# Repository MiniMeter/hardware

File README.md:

# hardware
MiniMeter PCB (designed in KiCad)

<div align="center">
    
</div>
<div align="center">
    
</div>
<div align="center">
    
</div>

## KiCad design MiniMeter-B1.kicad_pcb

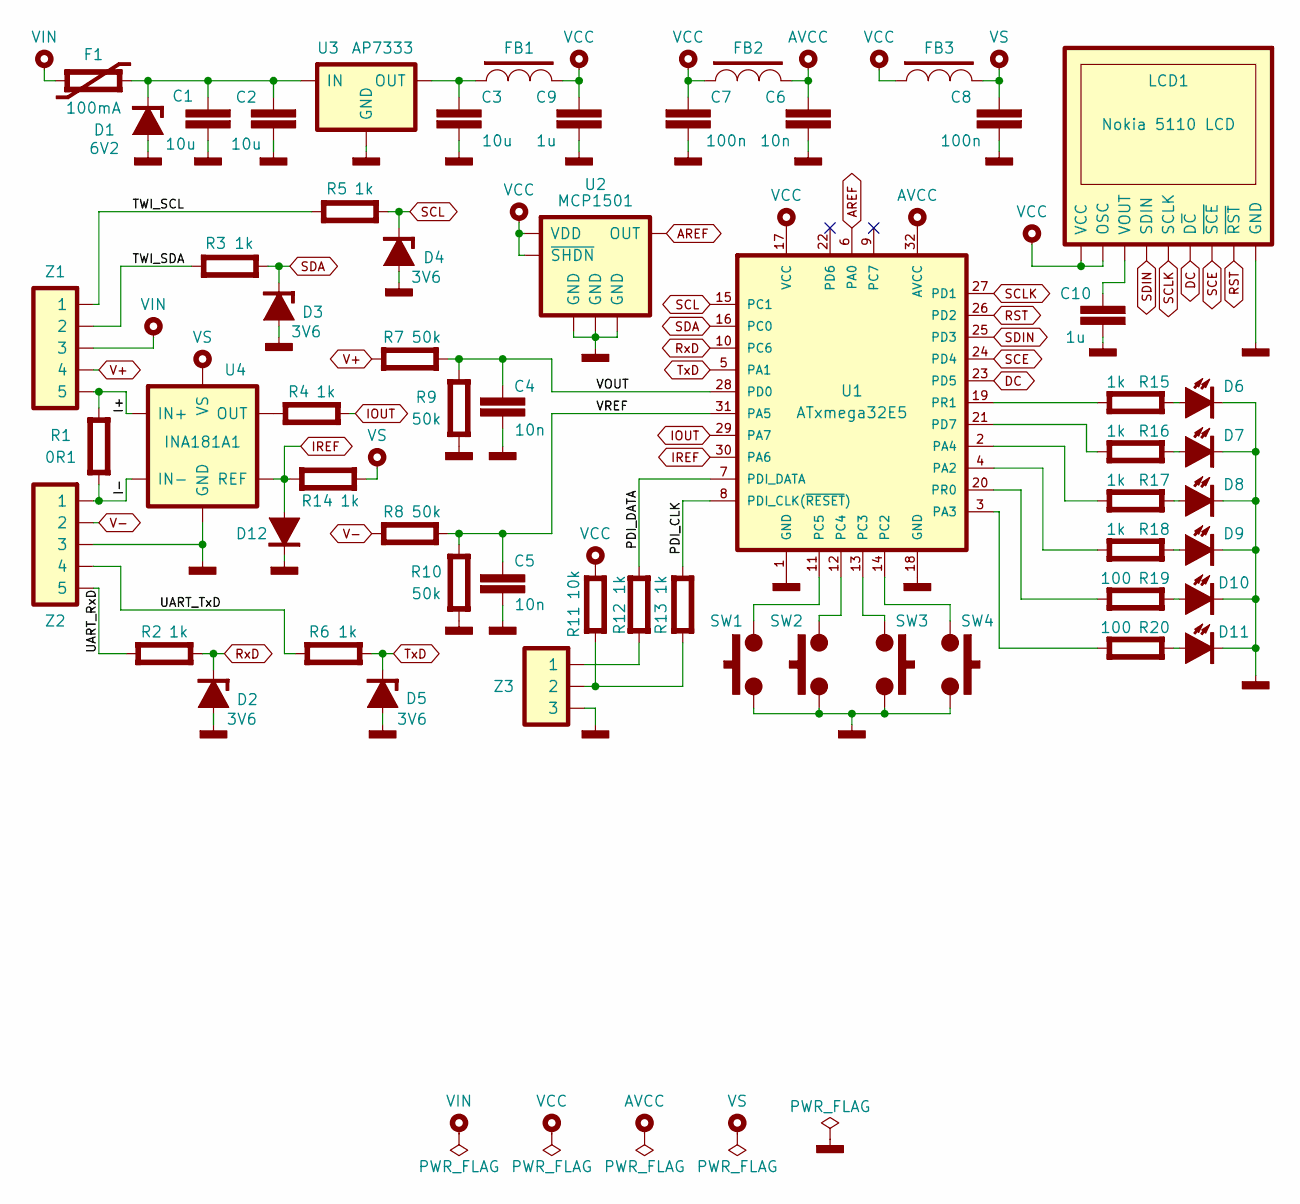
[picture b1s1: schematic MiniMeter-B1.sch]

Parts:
C1, C2, C3: 10u; SMD_2012_(0805)
C4, C5, C6: 10n; SMD_2012_(0805)
C7, C8: 100n; SMD_2012_(0805)
C9, C10: 1u; SMD_2012_(0805)
D1: 6V2; SMD_SOD-123
D2, D3, D4, D5: 3V6; SMD_SOD-323
D6, D7, D8, D9: LED-G; SMD_2012_(0805)+
D10, D11: LED-B; SMD_2012_(0805)+
D12: 1N4148; SMD_SOD-323
F1: 100mA; SMD_2012_(0805)
FB1, FB2, FB3: ferrite bead; SMD_2012_(0805)
LCD1: Nokia 5110 LCD; LCD_Nokia-5110
R1: 0R1; SMD_3216_(1206)
R2, R3, R4, R5, R6, R12, R13, R14, R15, R16, R17, R18: 1k; SMD_2012_(0805)
R7, R8, R9, R10: 50k; SMD_2012_(0805)
R11: 10k; SMD_2012_(0805)
R19, R20: 100; SMD_2012_(0805)
SW1, SW2, SW3, SW4: uSwitch 3x6mm; THT_uSwitch_3x6mm
U1: ATxmega32E5; SMD_TQFP-32_7x7mm
U2: MCP1501; SMD_SOT-23-6
U3: AP7333; SMD_SOT-23-3
U4: INA181A1; SMD_SOT-23-6
Z1, Z2: goldpin 1x5; THT_Goldpin-1x5
Z3: goldpin 1x3; THT_Goldpin-1x3

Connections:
/I+: R1.1, U4.3 (IN+), Z1.5
/I-: R1.2, U4.4 (IN-), Z2.1
/PDI_CLK: R13.2, U1.8 (PDI_CLK(~RESET~))
/PDI_DATA: R12.1, U1.7 (PDI_DATA)
/TWI_SCL: R5.2, Z1.1
/TWI_SDA: R3.2, Z1.2
/UART_RxD: R2.2, Z2.5
/UART_TxD: R6.2, Z2.4
/VOUT: C4.1, R7.1, R9.2, U1.28 (PD0)
/VREF: C5.1, R8.1, R10.2, U1.31 (PA5)
AREF: U1.6 (PA0), U2.1 (OUT)
AVCC: C6.1, FB2.2, U1.32 (AVCC)
DC: LCD1.6 (D~C), U1.23 (PD5)
GND: C1.2, C2.2, C3.2, C4.2, C5.2, C6.2, C7.2, C8.2, C9.2, C10.1, D1.2 (A), D2.2 (A), D3.2 (A), D4.2 (A), D5.2 (A), D6.1 (K), D7.1 (K), D8.1 (K), D9.1 (K), D10.1 (K), D11.1 (K), D12.1 (K), LCD1.3 (GND), R9.1, R10.1, SW1.2, SW2.2, SW3.2, SW4.2, U1.1 (GND), U1.18 (GND), U2.2 (GND), U2.3 (GND), U2.5 (GND), U3.3 (GND), U4.2 (GND), Z2.3, Z3.3
IOUT: R4.1, U1.29 (PA7)
IREF: D12.2 (A), R14.2, U1.30 (PA6), U4.5 (REF)
unnamed: C1.1, C2.1, D1.1 (K), F1.2, U3.1 (IN)
unnamed: C3.1, FB1.1, U3.2 (OUT)
unnamed: C10.2, LCD1.2 (VOUT)
unnamed: D6.2 (A), R15.2
unnamed: D7.2 (A), R16.2
unnamed: D8.2 (A), R17.2
unnamed: D9.2 (A), R18.2
unnamed: D10.2 (A), R19.2
unnamed: D11.2 (A), R20.2
unnamed: R4.2, U4.1 (OUT)
unnamed: R11.1, R13.1, Z3.2
unnamed: R12.2, Z3.1
unnamed: R15.1, U1.19 (PR1)
unnamed: R16.1, U1.21 (PD7)
unnamed: R17.1, U1.2 (PA4)
unnamed: R18.1, U1.4 (PA2)
unnamed: R19.1, U1.20 (PR0)
unnamed: R20.1, U1.3 (PA3)
unnamed: SW1.1, U1.11 (PC5)
unnamed: SW2.1, U1.12 (PC4)
unnamed: SW3.1, U1.13 (PC3)
unnamed: SW4.1, U1.14 (PC2)
RST: LCD1.1 (~RST), U1.26 (PD2)
RxD: D2.1 (K), R2.1, U1.10 (PC6)
SCE: LCD1.5 (~SCE), U1.24 (PD4)
SCL: D4.1 (K), R5.1, U1.15 (PC1)
SCLK: LCD1.8 (SCLK), U1.27 (PD1)
SDA: D3.1 (K), R3.1, U1.16 (PC0)
SDIN: LCD1.7 (SDIN), U1.25 (PD3)
TxD: D5.1 (K), R6.1, U1.5 (PA1)
V+: R7.2, Z1.4
V-: R8.2, Z2.2
VCC: C7.1, C9.1, FB1.2, FB2.1, FB3.1, LCD1.4 (OSC), LCD1.9 (VCC), R11.2, U1.17 (VCC), U2.4 (~SHDN), U2.6 (VDD)
VIN: F1.1, Z1.3
VS: C8.1, FB3.2, R14.1, U4.6 (VS)

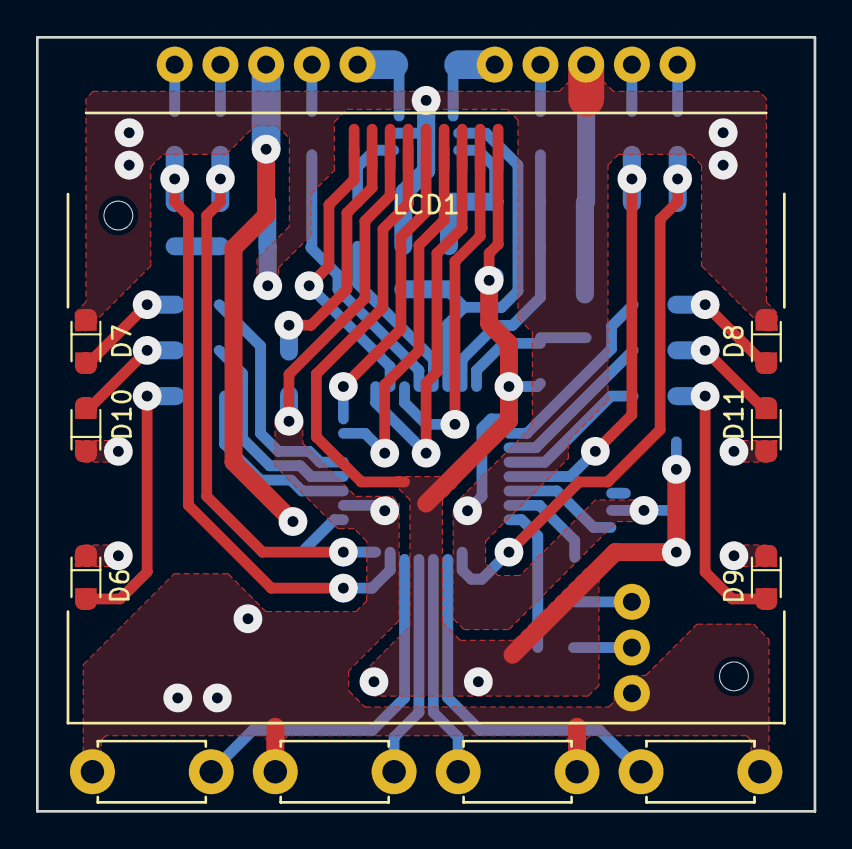
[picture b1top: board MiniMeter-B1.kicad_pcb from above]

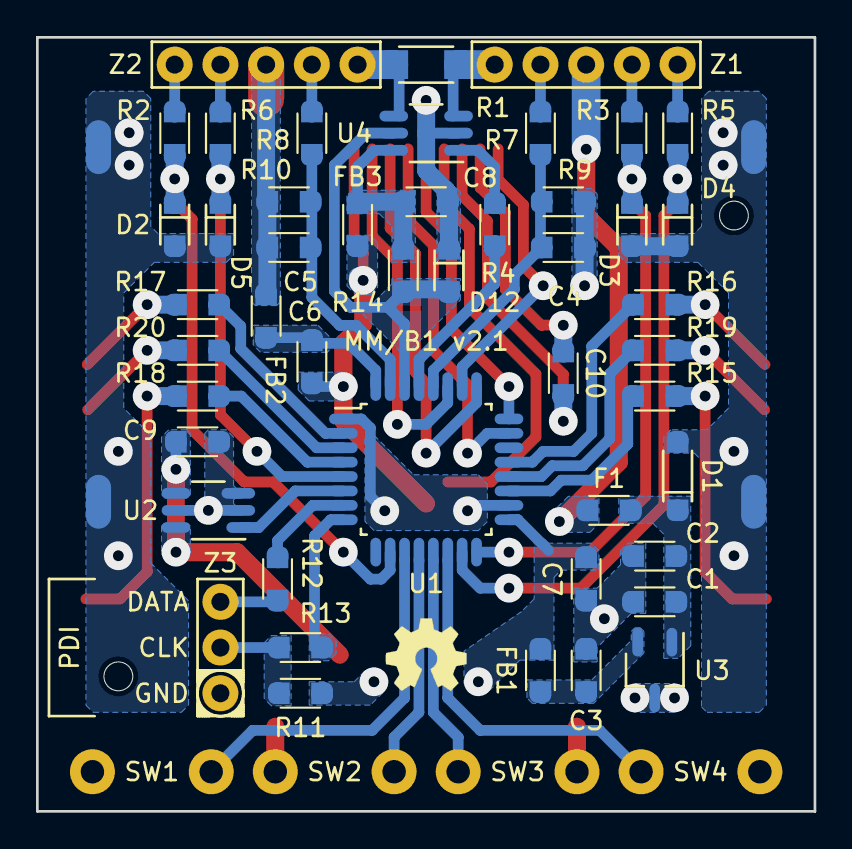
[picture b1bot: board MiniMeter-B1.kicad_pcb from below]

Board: 2 copper layers, 43.2 x 43.0 mm, 58 parts (47 on the bottom side), 51 nets.

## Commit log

2019-05-24 svg test
2019-05-24 jpg test
2019-05-24 jpg test 2
2019-05-24 svg/jpg test
2019-05-24 align center test
2019-05-24 pcb v2.1
2019-05-24 image scale test
2019-05-24 p -> div
2019-05-24 scaling
2019-05-26 ignore ods files
